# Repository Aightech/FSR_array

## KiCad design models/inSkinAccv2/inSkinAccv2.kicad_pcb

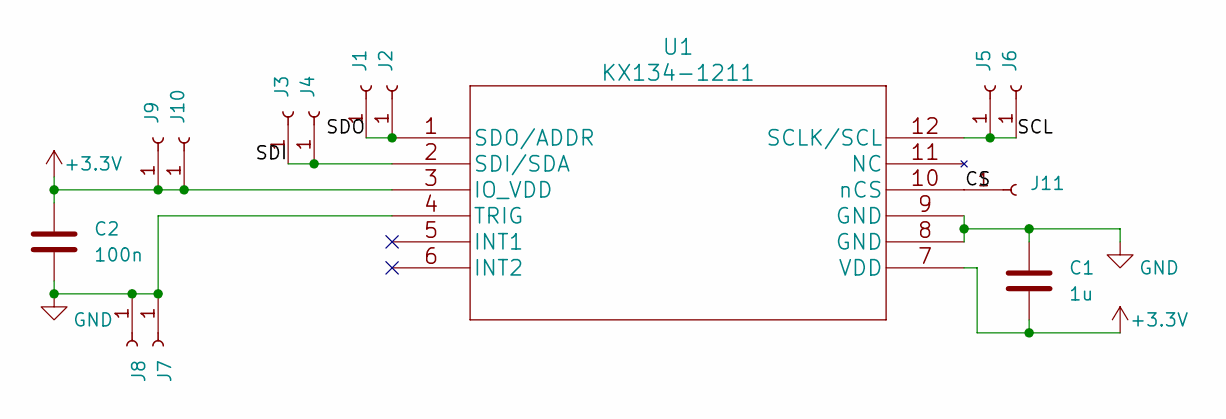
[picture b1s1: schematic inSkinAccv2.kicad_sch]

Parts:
C1: 1u; C_01005_0402Metric
C2: 100n; C_01005_0402Metric
J1, J2, J3, J4, J5, J6, J7, J8, J9, J10, J11: Conn_01x01_Female; SolderWirePad_1x01_SMD_1x2mm
U1: KX134-1211

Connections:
+3.3V: C1.2, C2.1, J9.1, J10.1, U1.3 (IO_VDD), U1.7 (VDD)
/CS: J11.1, U1.10 (nCS)
/SCL: J5.1, J6.1, U1.12 (SCLK/SCL)
/SDI: J3.1, J4.1, U1.2 (SDI/SDA)
/SDO: J1.1, J2.1, U1.1 (SDO/ADDR)
GND: C1.1, C2.2, J7.1, J8.1, U1.4 (TRIG), U1.8 (GND), U1.9 (GND)

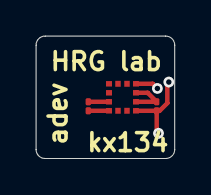
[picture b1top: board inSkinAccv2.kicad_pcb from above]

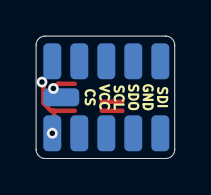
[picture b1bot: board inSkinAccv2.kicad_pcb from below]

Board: 2 copper layers, 7.7 x 6.8 mm, 14 parts (11 on the bottom side), 6 nets.

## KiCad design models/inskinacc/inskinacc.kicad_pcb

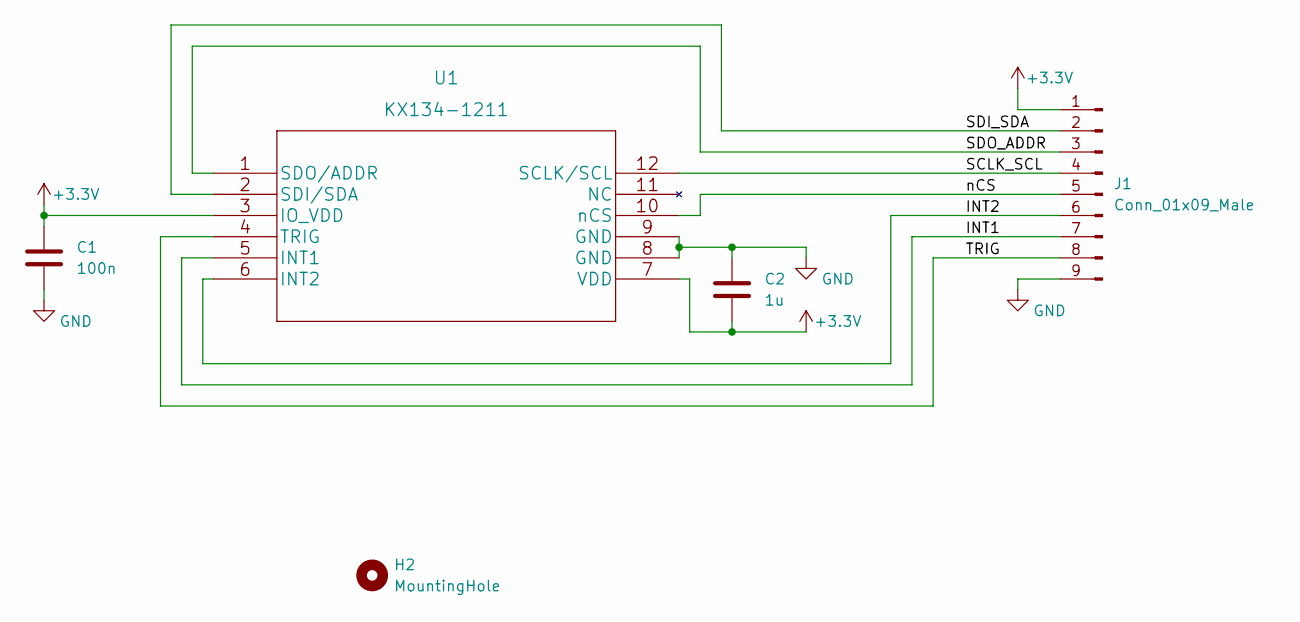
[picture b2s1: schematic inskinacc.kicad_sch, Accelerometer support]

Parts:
C1: 100n; C_01005_0402Metric
C2: 1u; C_01005_0402Metric
H2: MountingHole; MountingHole_2.2mm_M2
J1: Conn_01x09_Male; PinSocket_1x09_P1.27mm_Vertical
U1: KX134-1211

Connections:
+3.3V: C1.1, C2.2, J1.1, U1.3 (IO_VDD), U1.7 (VDD)
/INT1: J1.7, U1.5 (INT1)
/INT2: J1.6, U1.6 (INT2)
/SCLK_SCL: J1.4, U1.12 (SCLK/SCL)
/SDI_SDA: J1.2, U1.2 (SDI/SDA)
/SDO_ADDR: J1.3, U1.1 (SDO/ADDR)
/TRIG: J1.8, U1.4 (TRIG)
/nCS: J1.5, U1.10 (nCS)
GND: C1.2, C2.1, J1.9, U1.8 (GND), U1.9 (GND)

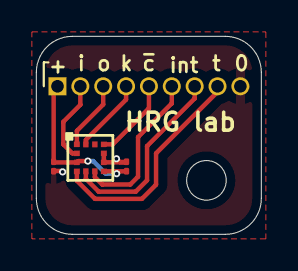
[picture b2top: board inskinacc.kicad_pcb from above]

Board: 2 copper layers, 12.5 x 11.0 mm, 5 parts (0 on the bottom side), 9 nets.

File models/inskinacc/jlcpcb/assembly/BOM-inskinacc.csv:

Comment,Designator,Footprint,LCSC
KX134-1211,U1,KX134-1211,
Conn_01x09_Male,J1,PinSocket_1x09_P1.27mm_Vertical,
1u,C2,C_01005_0402Metric,
100n,C1,C_01005_0402Metric,
MountingHole,H2,MountingHole_2.2mm_M2,

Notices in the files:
parts and their libraries:
Copyright 2021 Accelerated Designs. All rights reserved.
